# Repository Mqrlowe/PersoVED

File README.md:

# **Hello this is the ReadMe for my personnal github repo**

this repo contains mainly work for VED

### for the moment ts contains :
~~~
	PCB kicad projets
	CubeMx projetcs for the stm32
	A OneNote link to VED notes
~~~
### on the VED notes there is the following work :
~~~
	Can bus additionnal work to complete former studies
	regarding the can bus application in the FS architecture.
~~~

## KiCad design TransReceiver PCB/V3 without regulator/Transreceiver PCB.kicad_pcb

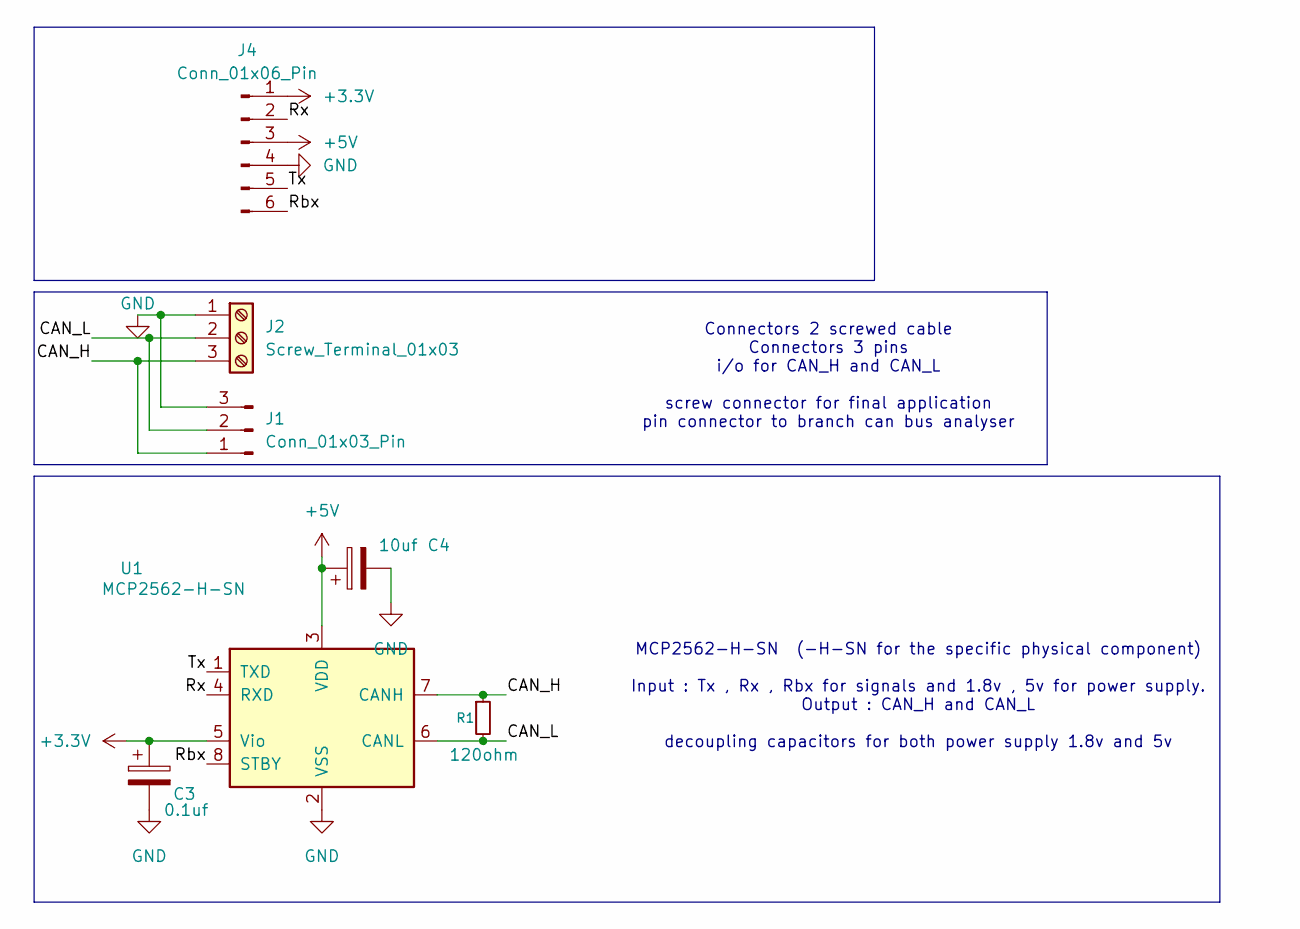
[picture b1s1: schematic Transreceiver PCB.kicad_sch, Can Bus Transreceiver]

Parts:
C3: 0.1uf; C_0805_2012Metric
C4: 10uf; C_0805_2012Metric
J1: Conn_01x03_Pin; PinSocket_1x03_P1.27mm_Vertical
J2: Screw_Terminal_01x03; TerminalBlock_Phoenix_MPT-0,5-3-2.54_1x03_P2.54mm_Horizontal
J4: Conn_01x06_Pin; PinHeader_1x06_P1.27mm_Horizontal
R1: 120ohm; R_0805_2012Metric
U1: MCP2562-H-SN; SOIC-8_3.9x4.9mm_P1.27mm

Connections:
+3.3V: C3.1, J4.1, U1.5 (Vio)
+5V: C4.1, J4.3, U1.3 (VDD)
/CAN_H: J1.1, J2.3, R1.1, U1.7 (CANH)
/CAN_L: J1.2, J2.2, R1.2, U1.6 (CANL)
/Rbx: J4.6, U1.8 (STBY)
/Rx: J4.2, U1.4 (RXD)
/Tx: J4.5, U1.1 (TXD)
GND: C3.2, C4.2, J1.3, J2.1, J4.4, U1.2 (VSS)

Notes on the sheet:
Connectors 2 screwed cable Connectors 3 pins i/o for CAN_H and CAN_L screw connector for final application pin connector to branch can bus analyser
MCP2562-H-SN (-H-SN for the specific physical component) Input : Tx , Rx , Rbx for signals and 1.8v , 5v for power supply. Output : CAN_H and CAN_L decoupling capacitors for both power supply 1.8v and 5v

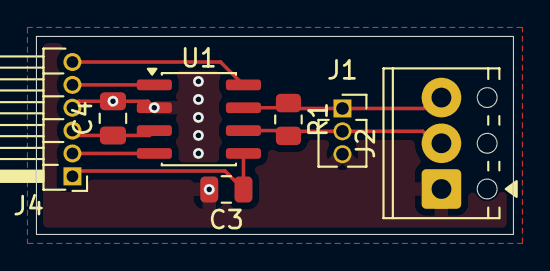
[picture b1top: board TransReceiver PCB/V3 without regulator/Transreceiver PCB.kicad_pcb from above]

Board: 2 copper layers, 26.5 x 11.0 mm, 7 parts (0 on the bottom side), 8 nets.

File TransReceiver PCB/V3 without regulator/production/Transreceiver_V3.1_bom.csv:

Designator,Footprint,Quantity,Value,LCSC Part #
C3,0805,1,0.1uf,
C4,0805,1,10uf,
J1,PinSocket_1x03_P1.27mm_Vertical,1,Conn_01x03_Pin,
J2,"TerminalBlock_Phoenix_MPT-0,5-3-2.54_1x03_P2.54mm_Horizontal",1,Screw_Terminal_01x03,
J4,PinHeader_1x06_P1.27mm_Horizontal,1,Conn_01x06_Pin,
R1,0805,1,120ohm,
U1,SOIC-8_3.9x4.9mm_P1.27mm,1,MCP2562-H-SN,

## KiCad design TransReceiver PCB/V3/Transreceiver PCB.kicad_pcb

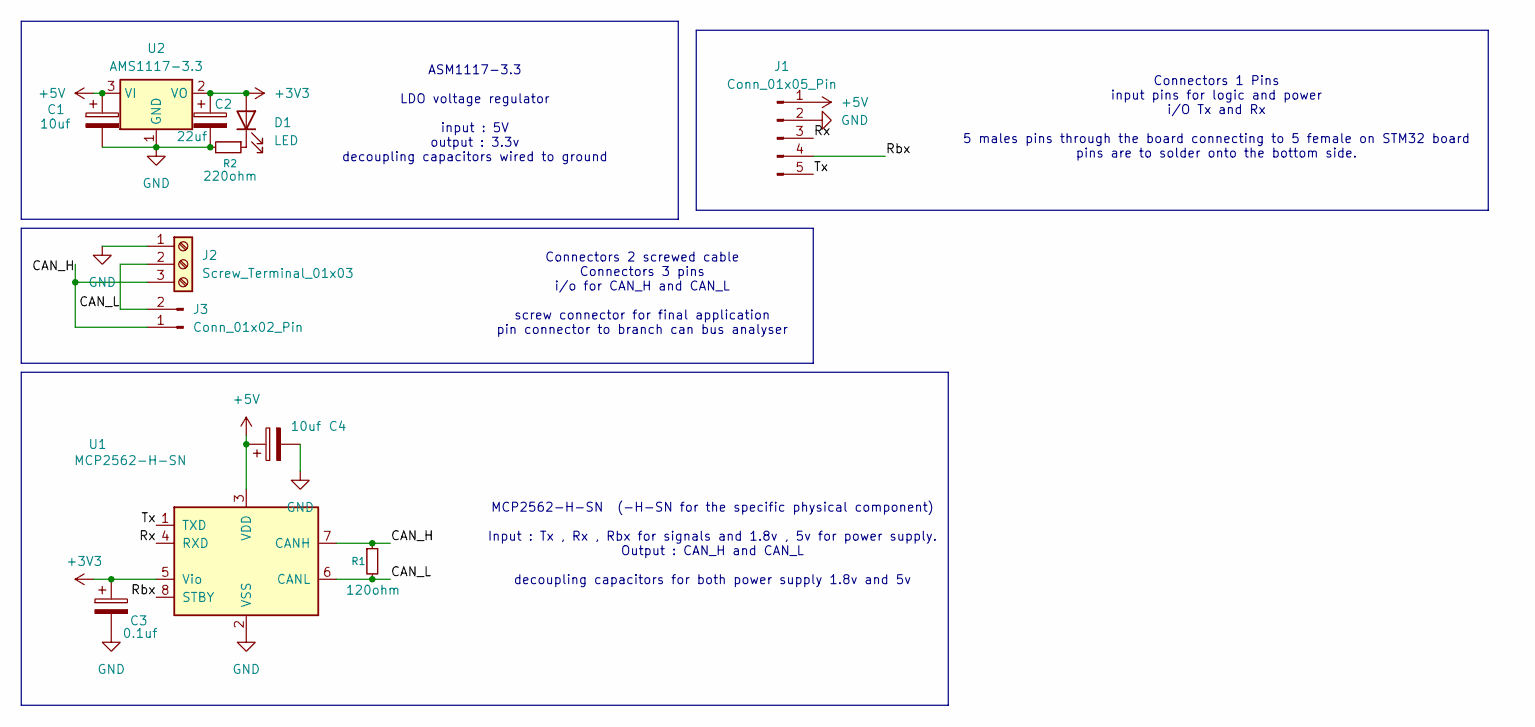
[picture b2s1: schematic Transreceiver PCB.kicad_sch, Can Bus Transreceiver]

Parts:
C1, C4: 10uf; C_0805_2012Metric
C2: 22uf; C_0805_2012Metric
C3: 0.1uf; C_0805_2012Metric
D1: LED; LED_0805_2012Metric
J1: Conn_01x05_Pin; PinHeader_1x05_P1.27mm_Horizontal
J2: Screw_Terminal_01x03; TerminalBlock_Phoenix_MKDS-1,5-3-5.08_1x03_P5.08mm_Horizont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
J3: Conn_01x02_Pin; PinHeader_1x02_P1.27mm_Vertical
R1: 120ohm; R_0805_2012Metric
R2: 220ohm; R_0805_2012Metric
U1: MCP2562-H-SN; SOIC-8_3.9x4.9mm_P1.27mm
U2: AMS1117-3.3; SOT-223-3_TabPin2

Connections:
+3V3: C2.1, C3.1, D1.2 (A), U1.5 (Vio), U2.2 (VO)
+5V: C1.1, C4.1, J1.1, U1.3 (VDD), U2.3 (VI)
/CAN_H: J2.3, J3.1, R1.1, U1.7 (CANH)
/CAN_L: J2.2, J3.2, R1.2, U1.6 (CANL)
/Rbx: J1.4, U1.8 (STBY)
/Rx: J1.3, U1.4 (RXD)
/Tx: J1.5, U1.1 (TXD)
GND: C1.2, C2.2, C3.2, C4.2, J1.2, J2.1, R2.2, U1.2 (VSS), U2.1 (GND)
unnamed: D1.1 (K), R2.1

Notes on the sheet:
ASM1117-3.3 LDO voltage regulator input : 5V output : 3.3v decoupling capacitors wired to ground
Connectors 2 screwed cable Connectors 3 pins i/o for CAN_H and CAN_L screw connector for final application pin connector to branch can bus analyser
MCP2562-H-SN (-H-SN for the specific physical component) Input : Tx , Rx , Rbx for signals and 1.8v , 5v for power supply. Output : CAN_H and CAN_L decoupling capacitors for both power supply 1.8v and 5v
Connectors 1 Pins input pins for logic and power i/O Tx and Rx 5 males pins through the board connecting to 5 female on STM32 board pins are to solder onto the bottom side.

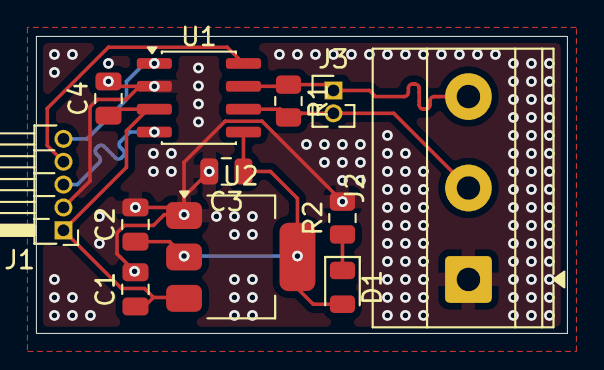
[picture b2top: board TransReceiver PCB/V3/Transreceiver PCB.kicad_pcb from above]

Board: 2 copper layers, 29.5 x 16.5 mm, 12 parts (0 on the bottom side), 9 nets.

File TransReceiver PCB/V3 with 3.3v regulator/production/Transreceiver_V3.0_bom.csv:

Designator,Footprint,Quantity,Value,LCSC Part #
"C1, C4",0805,2,10uf,
C2,0805,1,22uf,
C3,0805,1,0.1uf,
D1,0805,1,LED,
J1,PinHeader_1x05_P1.27mm_Horizontal,1,Conn_01x05_Pin,
J2,"TerminalBlock_Phoenix_MKDS-1,5-3-5.08_1x03_P5.08mm_Horizontal",1,Screw_Terminal_01x03,
J3,PinHeader_1x02_P1.27mm_Vertical,1,Conn_01x02_Pin,
R1,0805,1,120ohm,
R2,0805,1,220ohm,
U1,SOIC-8_3.9x4.9mm_P1.27mm,1,MCP2562-H-SN,
U2,SOT-223-3_TabPin2,1,AMS1117-3.3,

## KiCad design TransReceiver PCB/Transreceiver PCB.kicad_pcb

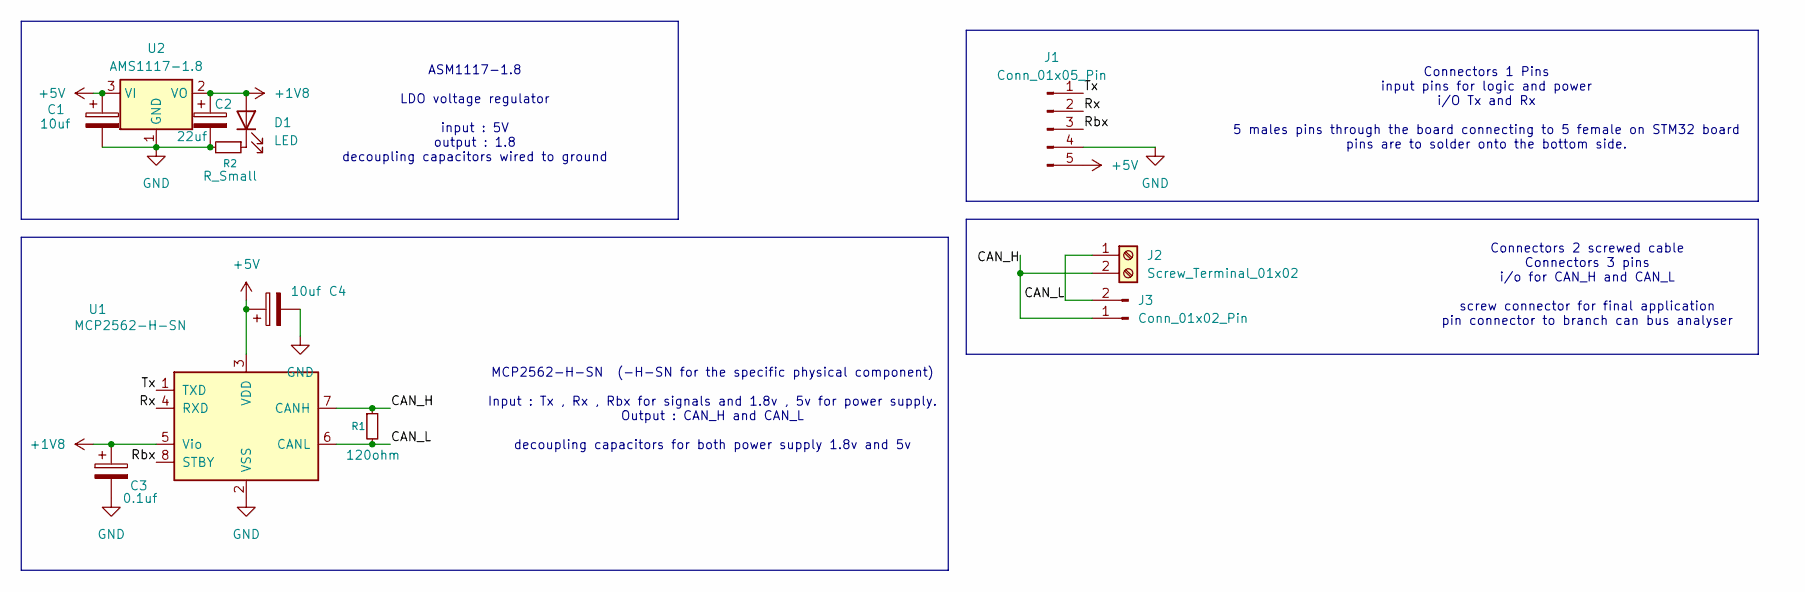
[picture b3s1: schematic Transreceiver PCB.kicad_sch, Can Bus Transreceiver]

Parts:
C1, C4: 10uf; C_0805_2012Metric
C2: 22uf; C_0805_2012Metric
C3: 0.1uf; C_0805_2012Metric
D1: LED; LED_0805_2012Metric
J1: Conn_01x05_Pin; PinHeader_1x05_P1.27mm_Vertical
J2: Screw_Terminal_01x02; TerminalBlock_Phoenix_PT-1,5-2-5.0-H_1x02_P5.00mm_Horizontal
J3: Conn_01x02_Pin; PinHeader_1x02_P1.27mm_Vertical
R1: 120ohm; R_0805_2012Metric
R2: R_Small; R_0805_2012Metric
U1: MCP2562-H-SN; SOIC-8_3.9x4.9mm_P1.27mm
U2: AMS1117-1.8; SOT-223-3_TabPin2

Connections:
+1V8: C2.1, C3.1, D1.2 (A), U1.5 (Vio), U2.2 (VO)
+5V: C1.1, C4.1, J1.5, U1.3 (VDD), U2.3 (VI)
/CAN_H: J2.2, J3.1, R1.1, U1.7 (CANH)
/CAN_L: J2.1, J3.2, R1.2, U1.6 (CANL)
/Rbx: J1.3, U1.8 (STBY)
/Rx: J1.2, U1.4 (RXD)
/Tx: J1.1, U1.1 (TXD)
GND: C1.2, C2.2, C3.2, C4.2, J1.4, R2.2, U1.2 (VSS), U2.1 (GND)
unnamed: D1.1 (K), R2.1

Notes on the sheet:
ASM1117-1.8 LDO voltage regulator input : 5V output : 1.8 decoupling capacitors wired to ground
Connectors 2 screwed cable Connectors 3 pins i/o for CAN_H and CAN_L screw connector for final application pin connector to branch can bus analyser
MCP2562-H-SN (-H-SN for the specific physical component) Input : Tx , Rx , Rbx for signals and 1.8v , 5v for power supply. Output : CAN_H and CAN_L decoupling capacitors for both power supply 1.8v and 5v
Connectors 1 Pins input pins for logic and power i/O Tx and Rx 5 males pins through the board connecting to 5 female on STM32 board pins are to solder onto the bottom side.

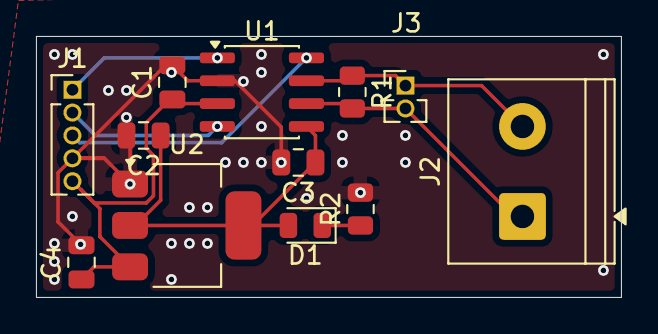
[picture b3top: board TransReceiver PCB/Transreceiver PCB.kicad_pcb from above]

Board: 2 copper layers, 32.5 x 14.5 mm, 12 parts (0 on the bottom side), 9 nets.
